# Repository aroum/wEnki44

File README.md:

# wEnki44

wEnki44 is a wireless version of Enki42 with a useless appendix.

Gerber files and STL models can be downloaded in [releases](https://github.com/aroum/wEnki44/releases).

## Typing

youtube video (click pic) by [@krikun98](https://github.com/krikun98)

## wEnki42

**Q:** Why is the pcb logo "wEnki42" even though the keyboard is called "wEnki44"?

**A:** This is a call to break off the useless appendix and use the [Watchman’s Layouts ](https://github.com/aroum/Watchman-layouts).

## Inspiration

* [nrfMicro](https://github.com/joric/nrfmicro)
* [Jian](https://github.com/KGOH/Jian-Info)
* [enki42](https://www.reddit.com/r/ErgoMechKeyboards/comments/qeq2qg/enki42_slim_ergo_keyboard/)
  
## Features

* 44/42 keys
* Kailh Choc V1 switches
* Choc spacing
* Direct pins 
* Wireless
* Full body Tenting case with magnets
* Power switch and reset button
* NFC tag

# Firmware

[wEnki44 zmk config](https://github.com/krikun98/zmk-config/tree/wEnki44) by [@krikun98](https://github.com/krikun98)

You can use firmware from [Jorian840](https://github.com/krikun98/jorian840), they are fully compatible. 

# BOM

| Item                                                                   | Quantity | Remarks                              |
| ---------------------------------------------------------------------- | -------: | ------------------------------------ |
| [Kailh Choc V1](https://aliexpress.ru/item/32959996455.html)           | 44/42    | switches                             |
| [Keycaps](https://aliexpress.ru/item/33026798318.html)                 | 44/42    | 1U (choc spacing)                    |
| [SMD button 3x4x2mm](https://aliexpress.ru/item/1005003812819985.html) | 2        | for reset                            |
| [MSK-12C02](https://aliexpress.ru/item/1005001398386692.html)          | 2        | Power switch                         |
| [702035](https://aliexpress.ru/item/1005003738158239.html)             | 2        | Or any battery size up to 21x47x8.8mm|
| [Magnets](https://aliexpress.ru/item/1005002757445161.html)            | 50-70    | disc 7x2 mm                          |
| [Bumpers](https://aliexpress.ru/item/4001188580018.html)               | 28       | 5x2 mm                               |
| [NFC-tag Ntag213](https://aliexpress.ru/item/1005001731694350.html)    | 1-2      | for top case                         |

[Holyiot 18010](https://aliexpress.ru/item/32951888809.html) is used as a BLE module. 

All everything else is the same to [nrfMicro](https://github.com/joric/nrfmicro/wiki/Components)

Interactive BOM is located ```/pcb/ibom```

# NFC

You can program an NFC tag to connect to a keyboard or open a KLE using the [NFC Tools](https://play.google.com/store/apps/details?id=com.wakdev.wdnfc) app

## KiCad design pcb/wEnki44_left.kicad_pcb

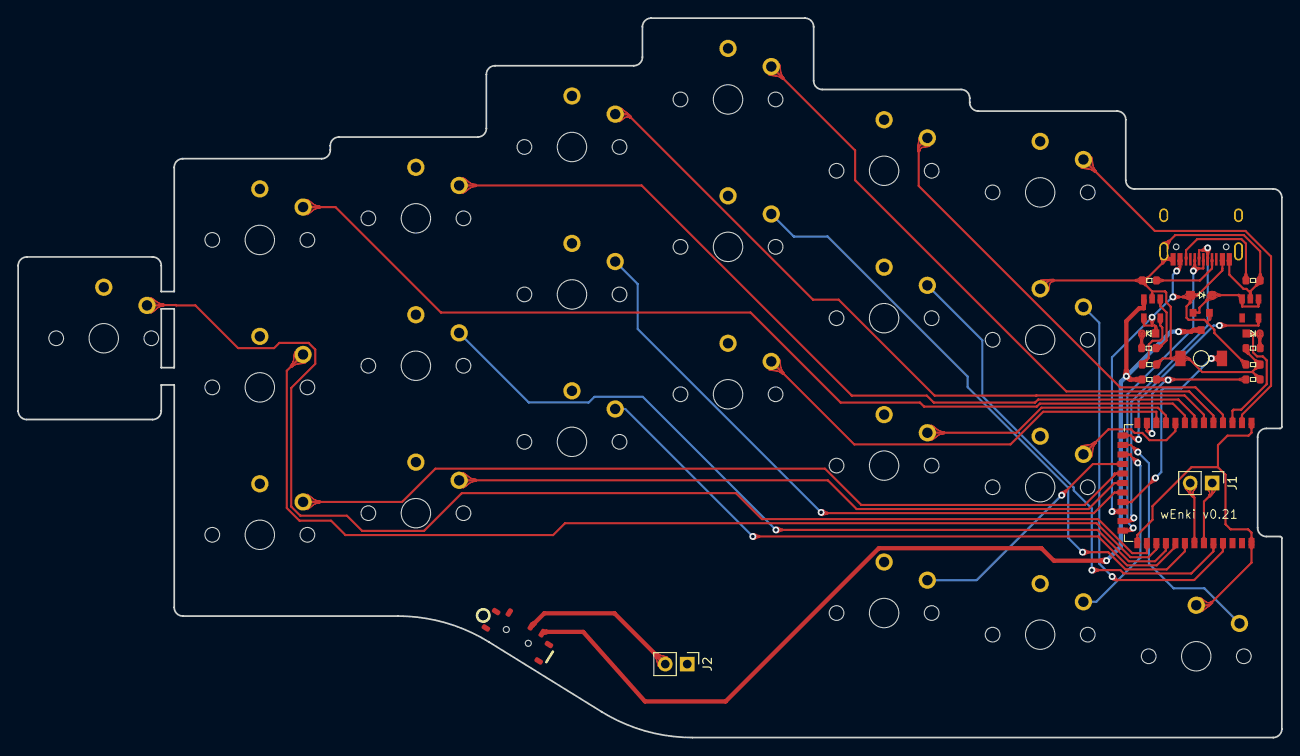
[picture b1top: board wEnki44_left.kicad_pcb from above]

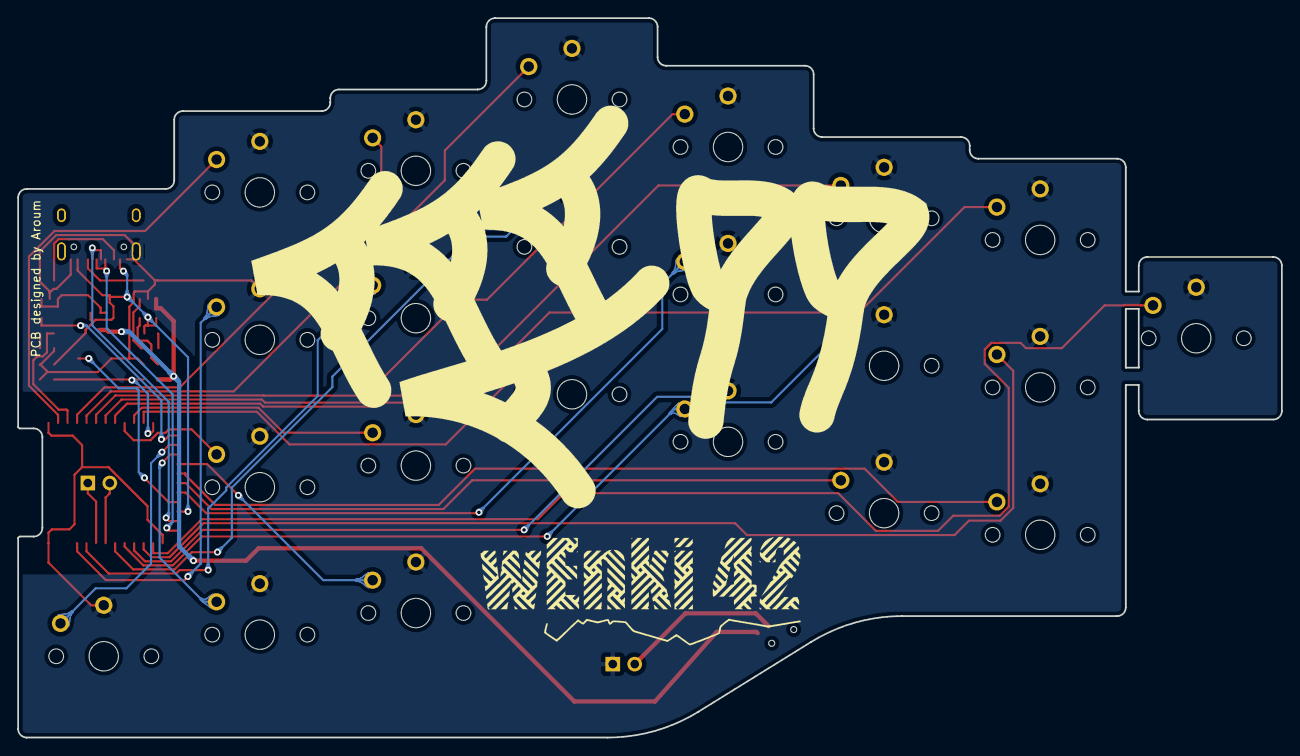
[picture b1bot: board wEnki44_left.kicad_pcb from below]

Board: 2 copper layers, 146.1 x 83.2 mm, 44 parts (2 on the bottom side), 41 nets.

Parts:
D22: RED; LED_0603_1608Metric
D23: BLUE; LED_0603_1608Metric
D24: 1N5819; D_SOD-323_HandSoldering
J1: SWD; PinHeader_1x02_P2.54mm_Vertical
J2: Ex_Bat; PinHeader_1x02_P2.54mm_Vertical
J3: USB-C Conn; USB_C_Receptacle_HRO_TYPE-C-31-M-12_round
Q1: AO3407; SOT-23
R1, R5: 1K; R_0603_1608Metric
R2: RPROG; R_0603_1608Metric
R3, R4: 5.1K; R_0603_1608Metric
R6: 100K; R_0603_1608Metric
R7: 820K; R_0603_1608Metric
R8: 2M; R_0603_1608Metric
RSW1: SW_PUSH; SW_3x4x2_2legs
SW1, SW2, SW3, SW4, SW5, SW6, SW7, SW8, SW9, SW10, SW11, SW12, SW13, SW14, SW15, SW16, SW17, SW18, SW19, SW20, SW21, SW23: SW_PUSH; ChocV1_1u
SW22: SW_SPDT; SW_MSK-12C02
U1: Holyiot-18010
U2: TP4054; SOT-23-5
U3: XC6220B331MR-G; SOT-23-5
logo1: Logo; Logo_wEnki42_mini
logoL1: Logo; Logo_42_big

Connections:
BATTERY_PIN: R7.2, R8.1, U1.12 (P0.04)
BLUE_LED: D23.2 (A), U1.3 (P1.10)
CC1: J3.A5 (CC1), R4.1
CC2: J3.B5 (CC2), R3.1
DATA+: J3.A6 (D+), J3.B6 (D+), U1.24 (D+)
DATA-: J3.A7 (D-), J3.B7 (D-), U1.23 (D-)
GND: J2.1, J3.A1 (GND), J3.A12 (GND), J3.B1 (GND), J3.B12 (GND), J3.S1 (SHIELD), R2.2, R3.2, R4.2, R5.2, R6.2, R8.2, RSW1.2, SW1.2, SW2.2, SW3.2, SW4.2, SW5.2, SW6.2, SW7.2, SW8.2, SW9.2, SW10.2, SW11.2, SW12.2, SW13.2, SW14.2, SW15.2, SW16.2, SW17.2, SW18.2, SW19.2, SW20.2, SW21.2, SW23.2, U1.1 (GND), U1.25 (GND), U1.37 (GND), U2.2 (VSS), U3.2 (GND)
unnamed: D22.1 (K), R1.1
unnamed: D23.1 (K), R5.1
unnamed: D24.1 (K), Q1.2 (S), U3.1 (VIN), U3.3 (EN)
unnamed: R1.2, U2.1 (STAT)
unnamed: R2.1, U2.5 (PROG)
R1C1: SW1.1, U1.8 (P0.28)
R1C2: SW2.1, U1.7 (P0.02)
R1C3: SW3.1, U1.6 (P0.03)
R1C4: SW4.1, U1.5 (P1.15)
R1C5: SW5.1, U1.4 (P1.13)
R1C6: SW6.1, U1.2 (P1.11)
R2C0: SW23.1, U1.26 (P0.22)
R2C1: SW7.1, U1.27 (P1.00)
R2C2: SW8.1, U1.28 (P1.03)
R2C3: SW9.1, U1.20 (P0.19)
R2C4: SW10.1, U1.30 (P1.02)
R2C5: SW11.1, U1.33 (P1.04)
R2C6: SW12.1, U1.34 (P1.06)
R3C1: SW13.1, U1.18 (P0.23)
R3C2: SW14.1, U1.19 (P0.21)
R3C3: SW15.1, U1.29 (P1.01)
R3C4: SW16.1, U1.11 (P0.31)
R3C5: SW17.1, U1.10 (P0.30)
R3C6: SW18.1, U1.9 (P0.29)
R4C5: SW19.1, U1.17 (P0.12)
R4C6: SW20.1, U1.16 (P1.09)
R4C7: SW21.1, U1.15 (P0.07)
SWC: J1.2, U1.31 (SWDCLK)
SWD: J1.1, U1.32 (SWDIO)
VBAT: J2.2, SW22.2 (B)
VBAT2: Q1.3 (D), R7.1, SW22.3 (C), U2.3 (VBAT)
VBUS: D22.2 (A), D24.2 (A), J3.A4 (VBUS), J3.A9 (VBUS), J3.B4 (VBUS), J3.B9 (VBUS), Q1.1 (G), R6.1, U1.22 (VBUS), U2.4 (VDD)
nRF_VDD: U1.14 (VDD_nRF), U3.5 (VOUT)
reset: RSW1.1, U1.21 (P0.18/RESET)

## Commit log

2022-09-24 init
